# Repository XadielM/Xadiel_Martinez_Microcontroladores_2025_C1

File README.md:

# Xadiel_Martinez_Microcontroladores_2025_C1
# Xadiel_Martinez_Microcontroladores_2025_C1
# Xadiel_Martinez_Microcontroladores_2025_C1

Hola hello

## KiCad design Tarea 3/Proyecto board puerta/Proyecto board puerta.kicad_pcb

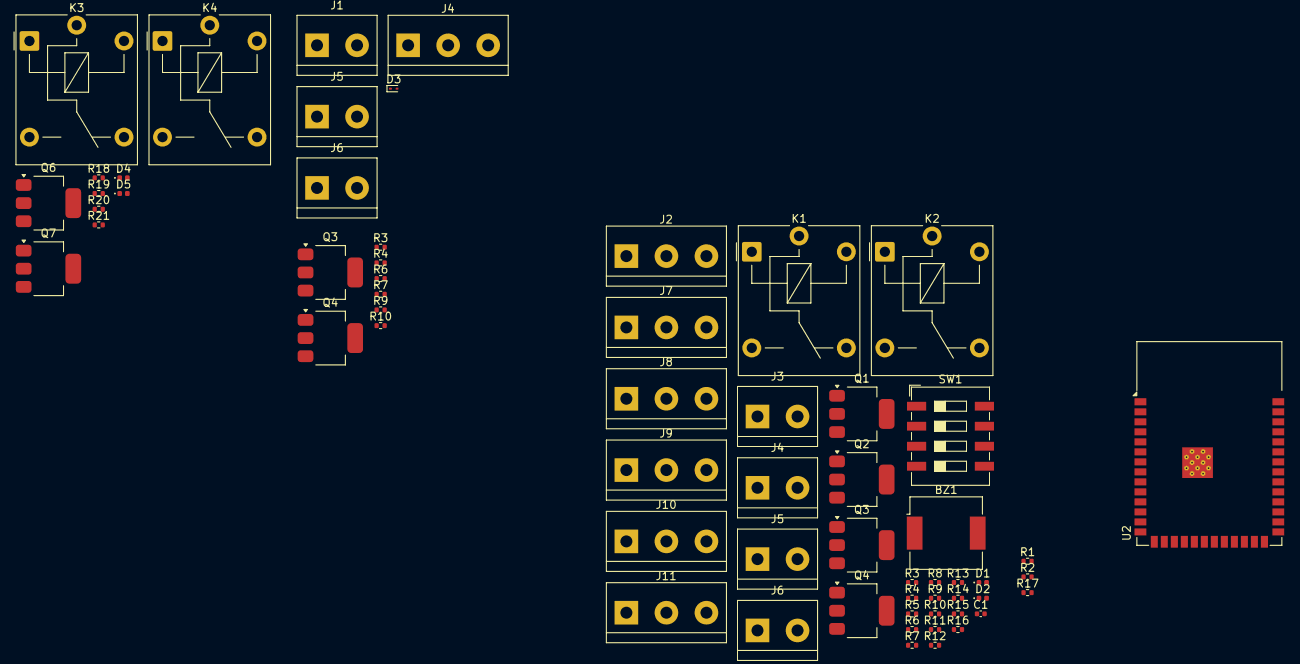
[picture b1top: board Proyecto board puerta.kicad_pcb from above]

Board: 2 copper layers, 62 parts (0 on the bottom side), 43 nets, no tracks yet.

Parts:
BZ1: Buzzer; Buzzer_CUI_CPT-9019S-SMT
C1: 22u; C_0402_1005Metric
D1, D4: CLOSED LED; LED_0402_1005Metric
D2, D5: OPEN LED; LED_0402_1005Metric
D3: ESD9B3.3ST5G; D_SOD-923
J1, J3: PP; TerminalBlock_bornier-2_P5.08mm
J2, J4#2: KEY; TerminalBlock_bornier-3_P5.08mm
J4, J5: Light; TerminalBlock_bornier-2_P5.08mm
J5#2: MOTOR; TerminalBlock_bornier-2_P5.08mm
J6: Buzzer; TerminalBlock_bornier-2_P5.08mm
J6#2: VIn; TerminalBlock_bornier-2_P5.08mm
J7: Fotocelda; TerminalBlock_bornier-3_P5.08mm
J8: Limit Switch; TerminalBlock_bornier-3_P5.08mm
J9: idk2; TerminalBlock_bornier-3_P5.08mm
J10: FTC; TerminalBlock_bornier-3_P5.08mm
J11: Motor; TerminalBlock_bornier-3_P5.08mm
K1, K3: Relay 2; Relay_SPDT_Finder_36.11
K2, K4: Relay 1; Relay_SPDT_Finder_36.11
Q1, Q2, Q3, Q3#2, Q4, Q4#2, Q6, Q7: PNP; SOT-223-3_TabPin2
R1: 22k; R_0402_1005Metric
R2, R3, R3#2, R4, R4#2, R5, R6, R6#2, R7, R7#2, R8, R9#2, R10, R10#2, R11, R13, R14, R15, R16, R17, R18, R20: 1k; R_0402_1005Metric
R9, R12, R19, R21: 220; R_0402_1005Metric
SW1: SW_DIP_x04; SW_DIP_SPSTx04_Slide_9.78x12.34mm_W8.61mm_P2.54mm
U2: ESP32-S3-WROOM-1

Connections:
+5V: BZ1.1 (+), C1.1, J4.2, J6#2.2, J7.3, K1.12, K1.A1, K2.12, K2.A1
/Board_Micro/MOTOR_LEFT: J11.3, R18.1, R19.2
/Board_Micro/MOTOR_RIGHT: J11.1, R20.1, R21.2
/Board_Micro/RST: D3.2 (A2), R1.1, U2.3 (EN)
/Board_Micro/to_Buzzer: J6.1, Q4.2 (C)
/Board_Micro/to_Light: J5.1, Q3#2.2 (C)
FTC: J7.2, R8.2
FTC_M: J10.2, R4#2.1
GND: C1.2, D1.1 (K), D2.1 (K), D3.1 (A1), D4.1 (K), D5.1 (K), J1.2, J2.1, J3.1, J4#2.3, J6#2.1, J7.1, J8.2, J10.3, K1.14, K2.14, K3.14, K4.14, Q1.3 (E), Q2.3 (E), Q3.3 (E), Q3#2.3 (E), Q4.3 (E), Q4#2.3 (E), Q6.3 (E), Q7.3 (E), SW1.5, SW1.6, SW1.7, SW1.8, U2.1 (GND), U2.40 (GND), U2.41 (GND)
KEYA: R3.2, R4.1, R5.1, R8.1, R13.1, R14.1, R15.1, R16.1
KEYA_M: J4#2.1, R7.1
KEYC_M: J4#2.2, R6.1
LSA_M: J8.1, R17.1
LSC_M: J8.3, R2.2
M1: J5#2.2, K2.11
M2: J5#2.1, K1.11
MA: R11.1, R12.2
MC: R9.2, R10.1
unnamed: BZ1.2 (-), Q1.2 (C)
unnamed: D1.2 (A), R9.1
unnamed: D2.2 (A), R12.1
unnamed: D4.2 (A), R19.1
unnamed: D5.2 (A), R21.1
unnamed: J2.2, R4.2
unnamed: J2.3, R3.1
unnamed: J4.1, Q2.2 (C)
unnamed: Q1.1 (B), R6#2.2
unnamed: Q2.1 (B), R7#2.2
unnamed: Q3.1 (B), Q3#2.1 (B), R9#2.2, R10.2
unnamed: K1.A2, Q3.2 (C)
unnamed: Q4.1 (B), Q4#2.1 (B), R10#2.2, R11.2
unnamed: K2.A2, Q4#2.2 (C)
unnamed: Q6.1 (B), R18.2
unnamed: K3.A2, Q6.2 (C)
unnamed: Q7.1 (B), R20.2
unnamed: K4.A2, Q7.2 (C)
unnamed: R14.2, SW1.2
unnamed: R13.2, SW1.1
unnamed: R15.2, SW1.3
unnamed: R16.2, SW1.4
PP: J3.2, R5.2
PP_M: J1.1, R3#2.1
VDD: J5.2, J6.2, J10.1, K3.12, K3.A1, K4.12, K4.A1, R1.2, R2.1, R3#2.2, R4#2.2, R6.2, R7.2, R17.2, U2.2 (3V3)

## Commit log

2025-01-22 Making changes
2025-01-22 Probando commit
2025-01-23 Subiendo la tarea 1
2025-02-06 Segunda tarea
2025-02-06 Tarea 2. Codigo y dibujo
2025-02-06 Dibujo maquina de estado
2025-02-14 Tarea del codigo de maquina de estado
2025-02-14 Codigo de la maquina de estado
2025-02-20 subiendo tarea
2025-03-06 Actualizando proyecto KiCAD
2025-03-26 Tarea 5
2025-04-25 Final Project
2025-04-29 Create Tarea5.c
    Main file de la tarea 5
2025-04-29 Tarea5.c
    Main file de la tarea 5
